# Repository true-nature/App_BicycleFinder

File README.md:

App_BicycleFinder
=================

Bicycle finder in parking area.
It works on TOCOS TWE-Lite.
You can find your bicycle by melody controlled by wireless remote commander.

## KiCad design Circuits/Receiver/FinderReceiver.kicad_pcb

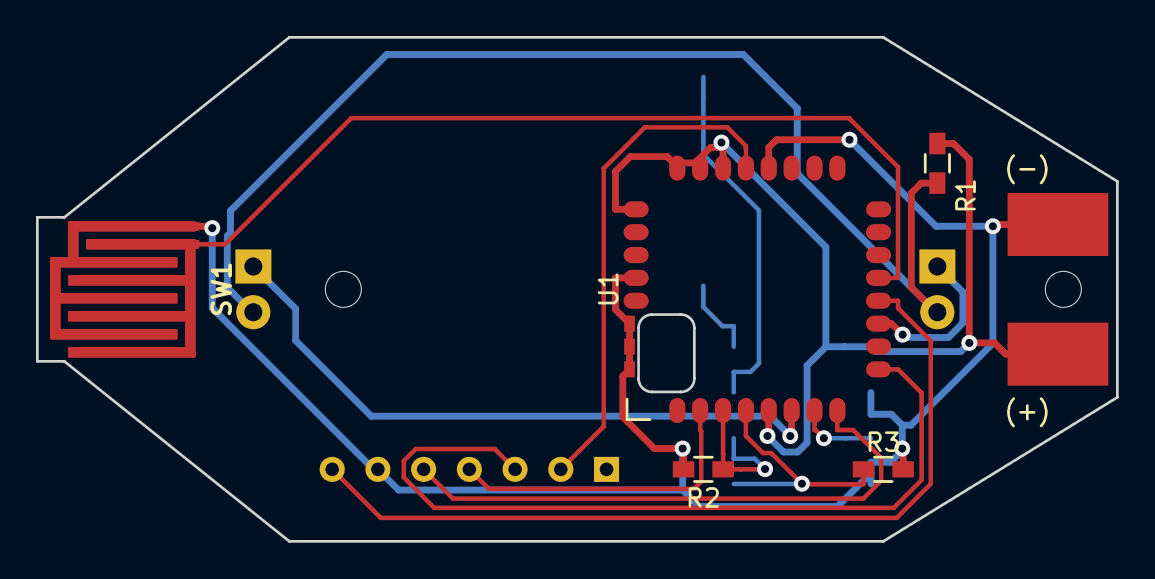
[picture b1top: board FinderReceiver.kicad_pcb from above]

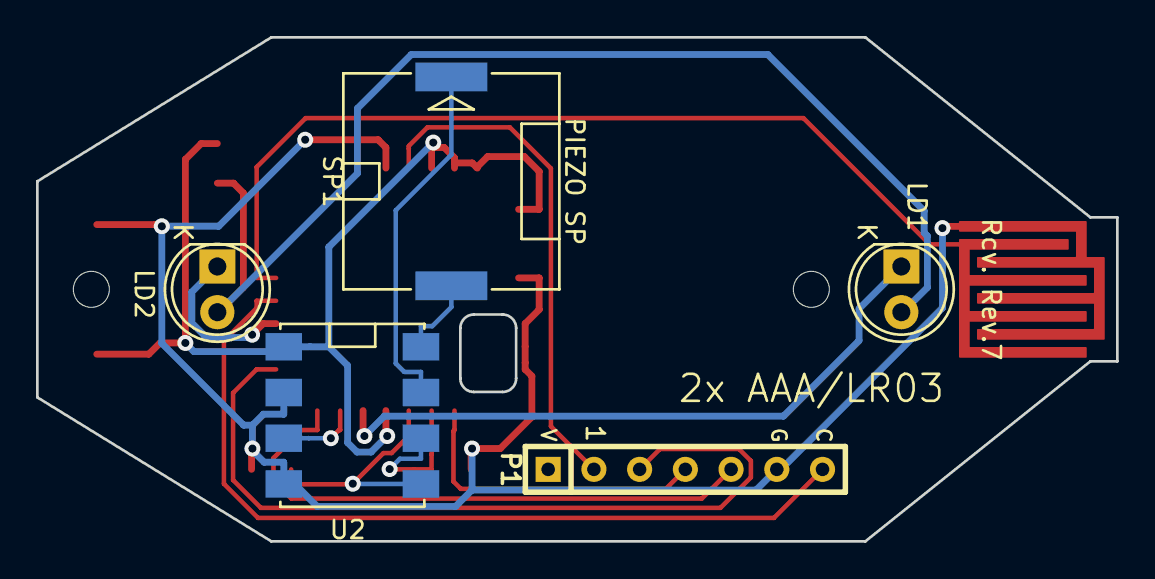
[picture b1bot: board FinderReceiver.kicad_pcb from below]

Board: 2 copper layers, 60.0 x 28.0 mm, 11 parts (6 on the bottom side), 16 nets.

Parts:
BT1: 2x AAA/LR03; FINDER_RECEIVER
LD1, LD2: LED; LED-5MM
P1: WRITER-VCC; WRITE-7P
R1: 680; R_0603_HandSoldering
R2, R3: 2M; R_0603_HandSoldering
SP1: PIEZO SP; PIEZOSPK
SW1: SW_PUSH; RUBBER_SWITCH
U1: TWE_LITE_SMD; TWE-001L-NC7
U2: NJU72501MJE; AE-NJU72501MJE

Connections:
/CFG: P1.6, U1.12
/DI1: SW1.1, U1.13
/DO3: LD1.1, U1.6
/DO4: LD2.1, U1.11
/EN1: R2.1, U1.3, U2.6
/EN2: R3.1, U1.4, U2.5
/LED: LD1.2, LD2.2, R1.2
/PRG: P1.3, U1.2
/RST: P1.1, U1.21
/RXD: P1.2, U1.9
/SOUND: U1.7, U2.3
/TXD: P1.4, U1.8
/VO1: SP1.1, U2.8
/VO2: SP1.2, U2.7
GND: BT1.2, P1.5, R2.2, R3.2, SW1.2, U1.20, U1.28, U1.30, U1.31, U1.32, U2.2, U2.4
VCC: BT1.1, R1.1, U1.5, U1.22, U1.23, U1.24, U1.25, U2.1

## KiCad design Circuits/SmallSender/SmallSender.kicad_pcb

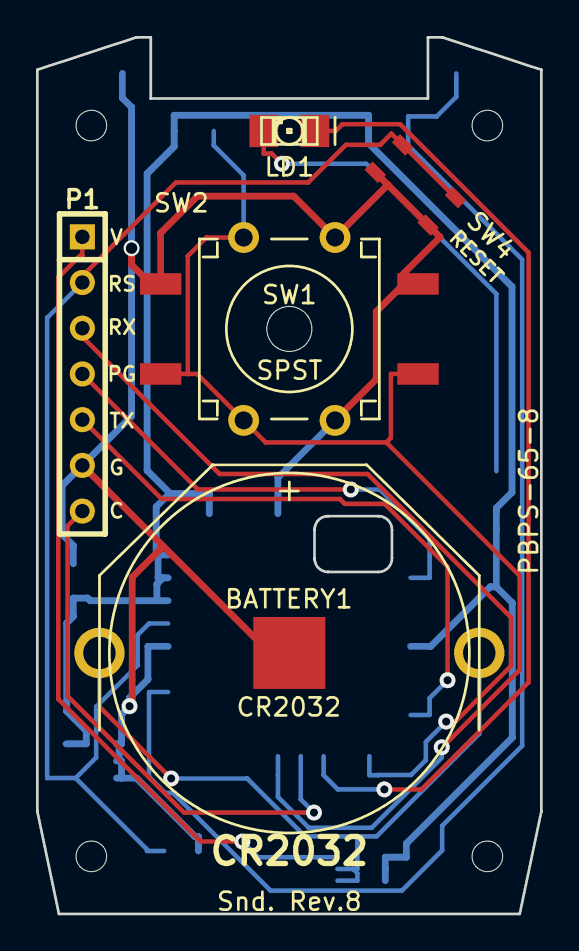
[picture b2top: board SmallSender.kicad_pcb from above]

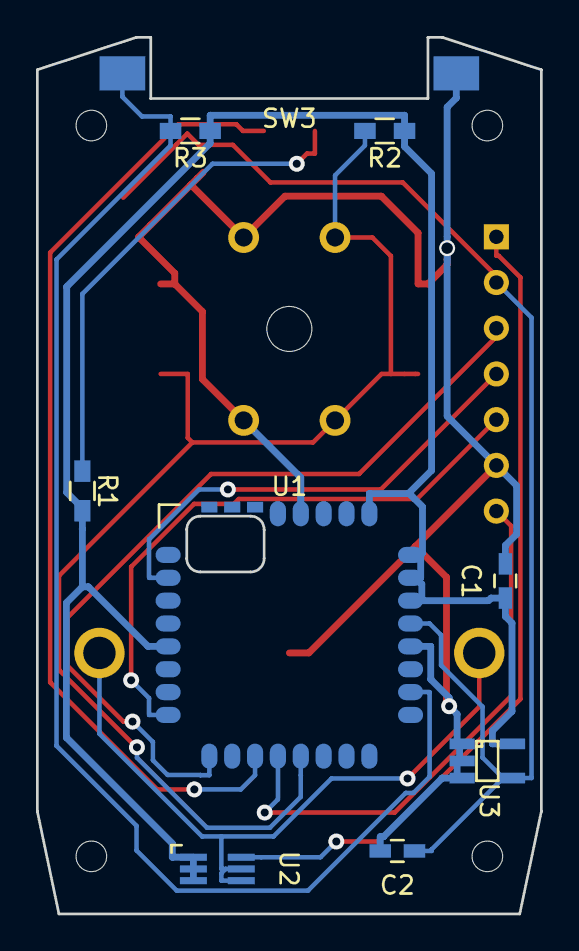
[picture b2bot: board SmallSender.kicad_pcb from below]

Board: 2 copper layers, 28.0 x 48.7 mm, 16 parts (9 on the bottom side), 13 nets.

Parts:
BATTERY1: CR2032; BK-888
C1: 10u; C_0603_HandSoldering
C2: 1000p; C_0603_HandSoldering
LD1: SML-012WT; LED-1206
P1: WRITER-VCC; WRITE-7P
PBPS-65-8: Snd. Rev.8; PBPS-65
R1: 680; R_0603_HandSoldering
R2, R3: 1M; R_0603_HandSoldering
SW1: SPST; B3FS-4002P_centerHole2_5mm
SW2: SPST; JB-15HFBP2
SW3: FR2S1015
SW4: SKRPACE010
U1: TWE_LITE_SMD; TWE-001L-NC7
U2: HN2S01FU; SC-70-6_Handsoldering
U3: BD45231G; SSOP5_Handsoldering

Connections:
/3V: BATTERY1.1, U2.4, U2.5
/CFG: P1.6, U1.12
/DI1: R2.2, SW1.1, SW2.1, U1.13
/DI4: R3.2, SW3.1, U1.18
/DO4: LD1.1, U1.11
/ExtVcc: P1.0, U2.6
/LED: LD1.2, R1.2
/PRG: P1.3, U1.2
/RST: C2.1, P1.1, SW4.1, U1.21, U3.4
/RXD: P1.2, U1.9
/TXD: P1.4, U1.8
/Vcc: C1.1, R1.1, R2.1, R3.1, U1.5, U1.22, U1.23, U1.24, U1.25, U2.1, U2.2, U2.3, U3.5
GND: BATTERY1.2, C1.2, C2.2, P1.5, SW1.2, SW2.2, SW3.2, SW4.2, U1.20, U1.28, U3.1, U3.2, U3.3

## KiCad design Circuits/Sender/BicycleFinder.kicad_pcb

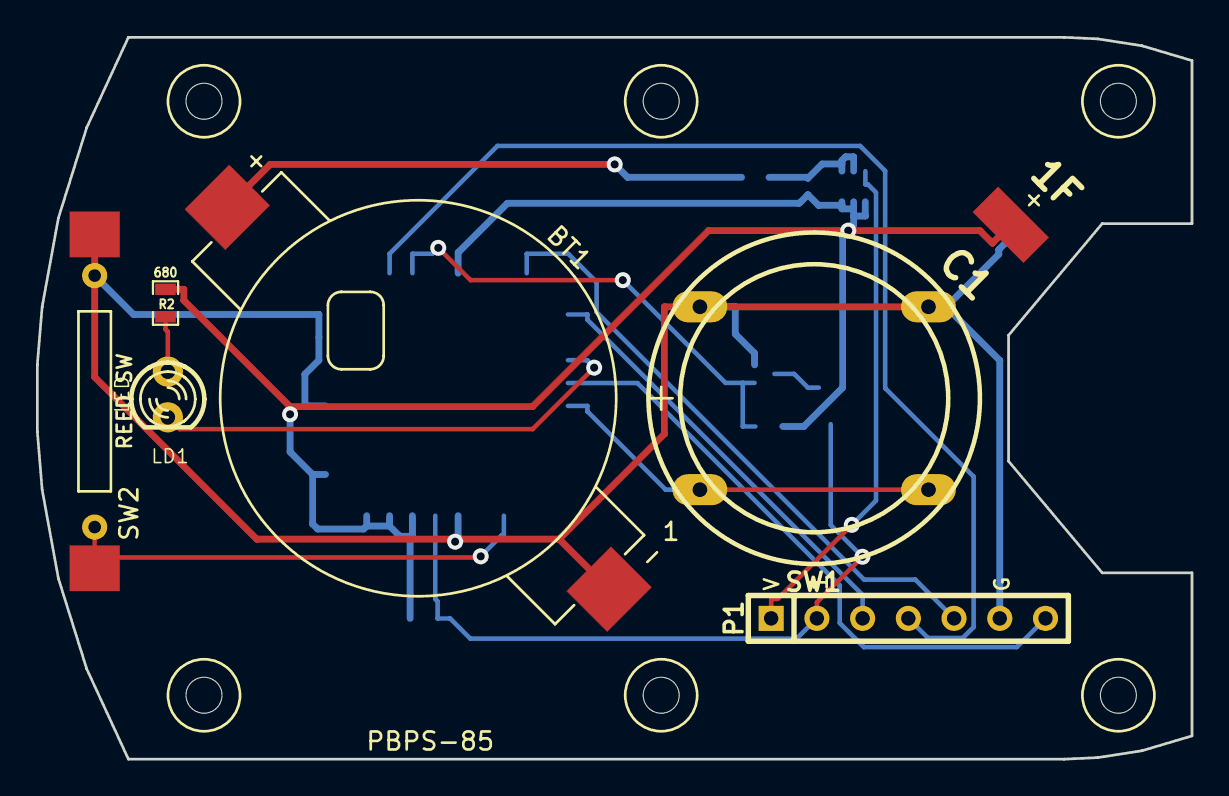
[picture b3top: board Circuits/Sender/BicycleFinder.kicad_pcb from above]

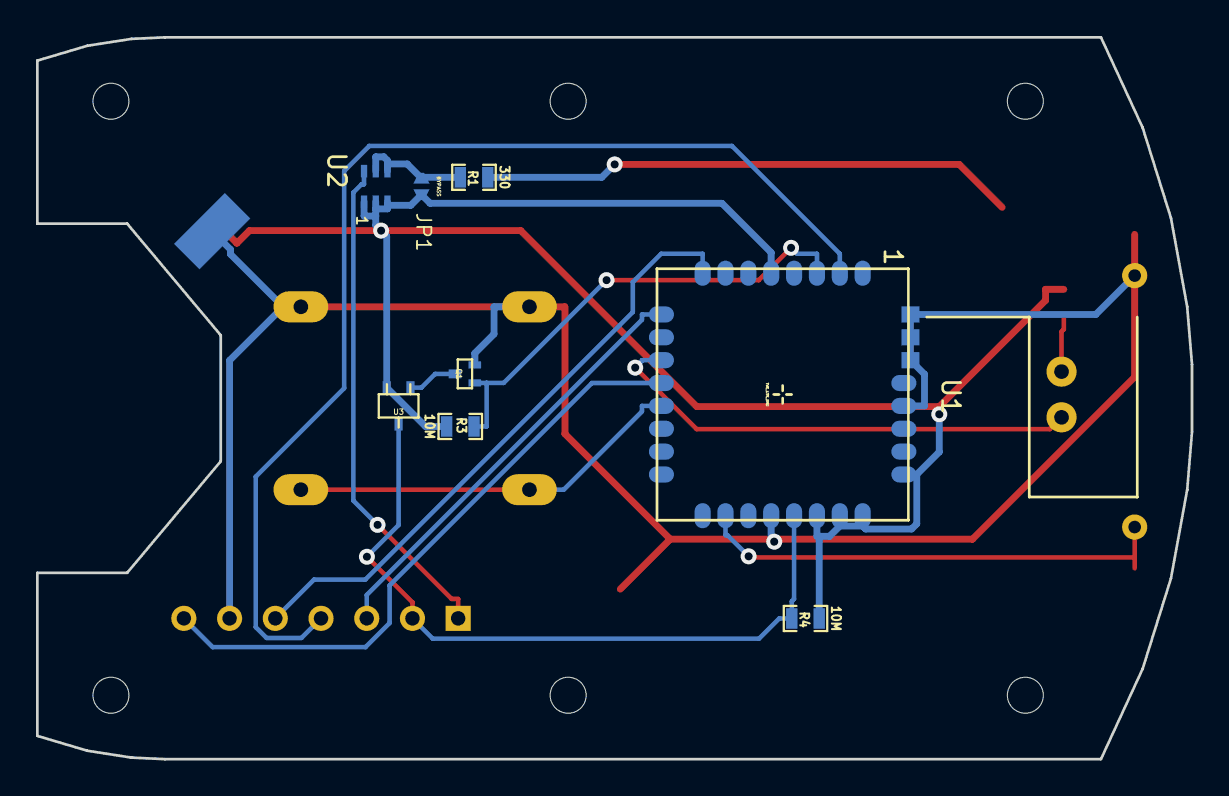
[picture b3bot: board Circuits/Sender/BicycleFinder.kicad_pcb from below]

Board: 2 copper layers, 64.1 x 40.1 mm, 16 parts (8 on the bottom side), 16 nets.

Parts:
BT1: CR2032; SMTU2032
C1: 1F; SE-5R5-D105VYV
JP1: BYPASS; JUMPER
LD1: LED; LED-3MM
P1: WRITER-VCC; WRITE-7P
PBPS-85: PBPS-85-EDLC
Q1: MOS_N; EMT3
R1: 330; SM0603_Resistor
R2: 680; SM0603_Resistor
R3, R4: 10M; SM0603_Resistor
SW1: SW_PUSH; JF-15CKCBNP2
SW2: REED SW; REEDSW
U1: TWE_LITE_SMD; TWE-001L-SMD-noNTH
U2: HN2S01FU
U3: TCM809RVNB; sc70

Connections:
/3V: BT1.1, R1.1
/CFG: P1.6, U1.12
/CHG: JP1.2, R1.2, U2.4, U2.5
/DO1: Q1.G, R3.2, U1.3
/DO4: LD1.2, U1.11
/ExVcc: P1.0, U2.6
/LED: LD1.1, R2.2
/PRG: P1.3, U1.2
/QGND: Q1.D, U3.1
/RST: P1.1, R4.2, U1.21, U3.2
/RXD: P1.2, U1.9
/STOP: SW2.1, U1.18
/TXD: P1.4, U1.8
/Vcc: C1.1, JP1.1, R2.1, R3.1, R4.1, U1.5, U1.22, U1.23, U1.24, U1.25, U2.1, U2.2, U2.3, U3.3
/WUP: SW1.1, U1.13
GND: BT1.2, C1.2, P1.5, Q1.S, SW1.2, SW2.2, U1.20, U1.28, U1.30, U1.31, U1.32

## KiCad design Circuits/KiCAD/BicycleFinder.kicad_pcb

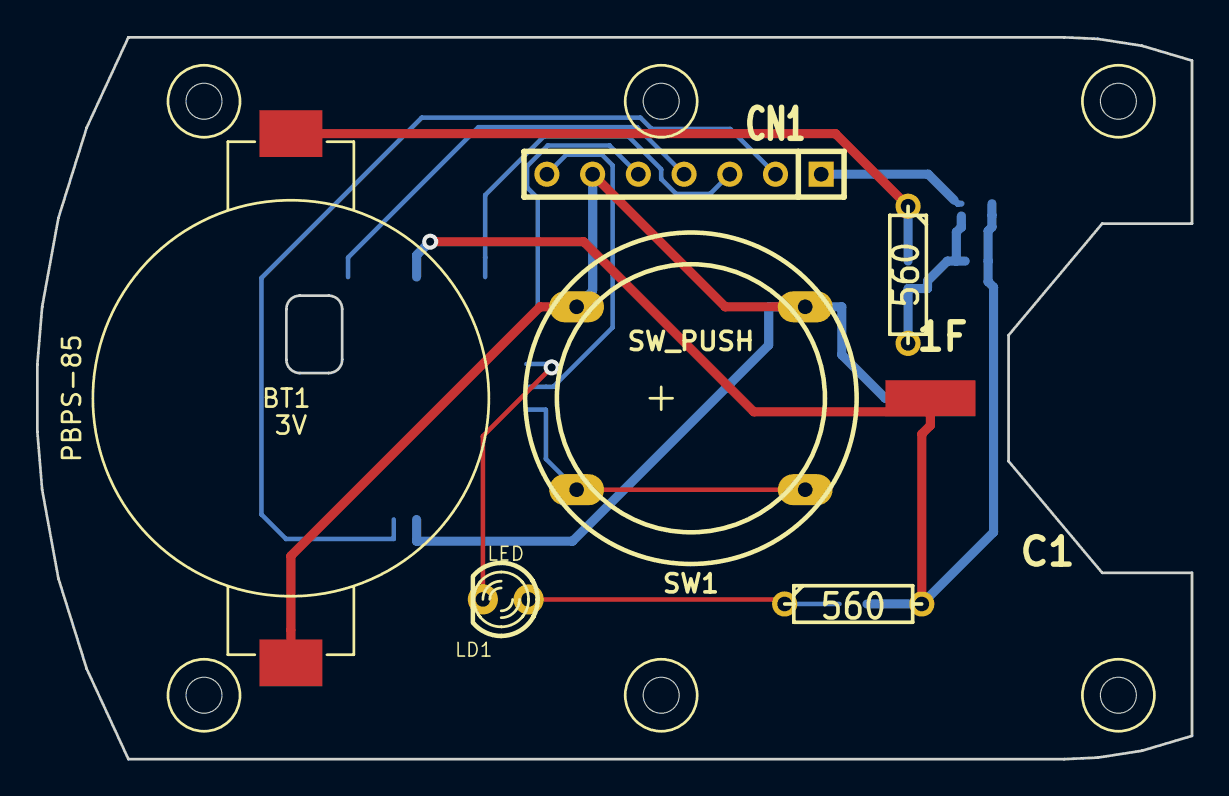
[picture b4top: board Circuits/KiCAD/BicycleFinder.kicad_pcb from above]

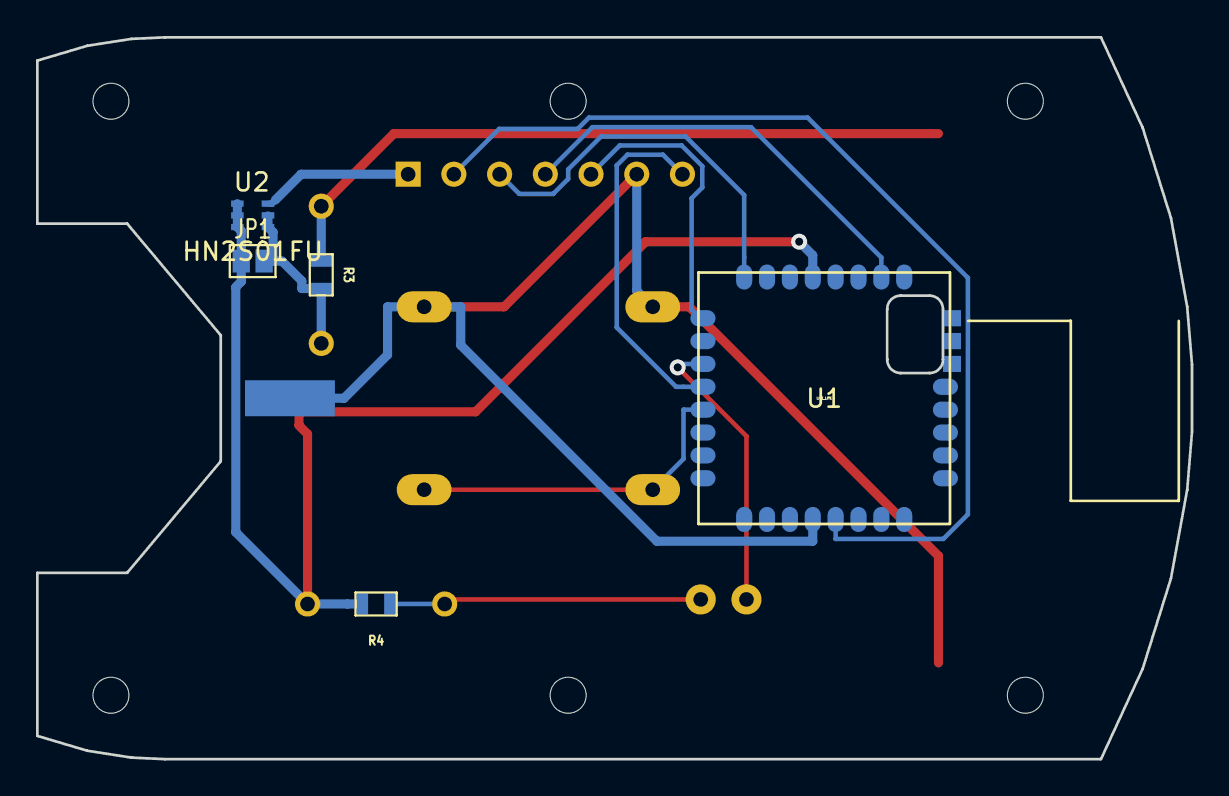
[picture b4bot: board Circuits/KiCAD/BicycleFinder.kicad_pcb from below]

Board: 2 copper layers, 64.1 x 40.1 mm, 13 parts (5 on the bottom side), 13 nets.

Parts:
BT1: 3V; SMTU2032
C1: 1F; SE-5R5-D105VYV
CN1: WRITER; SIL-7
JP1: BYPASS; GS2
LD1: LED; LED-3MM
PBPS-85: PBPS-85-EDLC
R1, R2: 560; R3
R3, R4: 560; SM0603
SW1: SW_PUSH; JF-15CKCBNP2
U1: LITE_LITE; TWE-001L-SMD
U2: HN2S01FU

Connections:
/3V: BT1.1, R1.1, R3.1
/CHG: JP1.2, R1.2, R3.2, U2.4, U2.5
/DC3V: CN1.1, U2.6
/DI1: SW1.1, U1.13
/DO4: LD1.2, U1.11
/LED: LD1.1, R2.1, R4.1
/M1: CN1.7, U1.12
/PRG: CN1.4, U1.2
/RST: CN1.2, U1.21
/RX: CN1.3, U1.8
/TX: CN1.5, U1.9
/Vcc: C1.1, JP1.1, R2.2, R4.2, U1.5, U2.1, U2.2, U2.3
GND: BT1.2, C1.2, CN1.6, SW1.2, U1.20

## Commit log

2014-09-09 App_TweLite 1.7から派生。
2014-09-09 Rename application from App_Twelite to App_BicycleFinder.
2014-09-09 Start to merge App_Melody.
2014-09-10 Merged MML implementation from App_Melody 1.3.3.
2014-09-10 スリープ抑止を開放するため、再生終了時にbHoldPlayをFALSEに変える。
2014-09-10 シリアル番号をベースにした独自のAPP_IDへ変更。
2014-09-10 1秒スリープでの受信処理を有効化。 メロディ再生中はスリープを抑止。
2014-09-10 改造部分を ENABLE_RX_ON_SLP_1SEC で切り分けた。
2014-09-10 リリースノートを独自内容に変更。
2014-09-10 Fixed typo.
2014-09-10 再生の終了待ちを独立した状態に分離。
2014-09-10 再生待ちを行うユーザー定義状態を新設。 再生の最大時間を60秒に制限。
2014-09-13 3曲目のメロディをHappy Birthdayに変更。
2014-09-13 間欠受信に失敗。
2014-09-13 他のdefineにあわせてUSE_RX_ON_SLP_1SECにrename。
2014-09-13 誤って除隊したSILENT_MODEの受信処理スキップを元に戻した。
2014-09-13 Revert "誤って除隊したSILENT_MODEの受信処理スキップを元に戻した。"
    This reverts commit 6c30a227d46dbb01fb6ffa2821d9764f91923357.
2014-09-13 SILENT_MODEと誤認して戻した変更を戻した。
2014-09-14 再生中で無い場合にLEDが一瞬点滅する場合があるバグを修正。
2014-09-14 バッテリー電圧が低下したときに点滅周期を短くする機能を追加。
2014-09-16 連続モードでもLEDを点滅させるようにした。
2014-09-17 状態遷移のタイミングをUARTに出力
2014-09-18 ADC無効化オプションが指定された場合、電源電圧だけをADC対象とする。 子機間欠モードでADC実行間隔を延長できるようにした。
2014-09-18 ADCスキップ時に受信時間を確保する。
2014-09-18 受信待ちを独立した状態で確保。
2014-09-18 連続送信を毎秒64回に増やしてWakeUp時間を減らした。
2014-09-22 再生終了時は無条件に割り込み時の再生処理を無効とする。
2014-09-22 リモコン側を子機間欠10秒モードで使用。
2014-09-23 mode4の通信間隔デフォルト値を4秒に延長。
2014-09-23 改造結果をリリースノートに反映。
2014-09-23 Bsch3vで描いた回路図を追加。
2014-09-24 SMD(QFN)版回路図を追加。
2014-09-24 QFN版DO4,GND配線ミスを修正。
2014-09-24 RESET SWを記入。
2014-09-25 未使用の宣言を削除。
2014-09-25 誤ったstatic修飾を削除。
2014-10-01 Moved circuit diagram to subdirectory.
2014-10-14 子機から子機への通信を、宛先IDによって有効とする。
2014-12-14 Restore u8Channel from EEPROM.
2014-12-15 Change operation mode to 3,4 or 7 by Device Id.
2014-12-15 Removed pull-up of analog input. Added program writer connector.
2014-12-15 Added SMD version of sender circuit.
2014-12-15 Renamed QFN to SMD.
2014-12-15 Implementing user defined MML data.
2014-12-15 Play MML in EEPROM as 1st index.
2014-12-16 コマンド0x95,0x96でMMLデータのread/writeを定義。
2014-12-16 Read/Write MML data between EEPROM and buffer.
2014-12-16 Added ToDo comments.
2014-12-16 Removed an unnecessary function.
2014-12-16 Save user MML data aligned to EEPROM segments.
2014-12-17 Fixed: Incompatible pointer.
2014-12-18 Reduced wires.
2014-12-18 Fixed: EEPROM were overwritten.
2014-12-19 Updated PNG images.
2014-12-19 Created KiCAD project file.
2014-12-19 Fit default value of the option bit for bicycle finder.
2014-12-19 Set destination id to children if sender was remote controller of bicycle finder.
2014-12-19 User more LEDs.
2014-12-20 Inverted octave up/down characters.
2014-12-20 Changed music index from FLASH[2] to EEPROM[0].
2014-12-20 Increased max length of MML string.
2014-12-20 Blink LED3, like LED4.
2014-12-20 EEPROM utility functions can read/write more than 64 bytes.
2014-12-20 子機間欠モードでチャンネル指定が有効になるようにした。
2014-12-20 Added description in header comment.
2014-12-22 Fixed: MML data was shorten before save.
2014-12-22 Disable RxEvent if mode 7(10 sec sleep mode).
2014-12-22 Split ProcessEv. vProcessEvCoreSlpSender for sender, and vProcessEvCoreSlpBeacon for receiver. Send only if bWakeupByButton is true.
2014-12-22 Continuous transmission is allowed if battery level is sufficient.
2014-12-22 Replaced voltage values to macro.
2014-12-22 Play MML only if 1sec sleep mode(mode 4).
2014-12-22 ProcessEv was opposite for mode 4 and mode 7.
2014-12-22 bWakeupByButton is not reliable. Determine to repeat or not by EDLC voltage.
2014-12-23 Saved new MML data.
2014-12-24 Updated KiCAD data.
2014-12-25 ERC passed.
2014-12-25 Added parentheses. Static analysis says that it may be a bug.
2014-12-25 Down one octave.
2014-12-25 Added arranged Canon.
2014-12-30 Made an example layout.
2015-01-04 CS75サイズ検討中。
2015-01-06 Inserted a register to reduce discharge current from CR2032.
2015-01-07 Changed pad shape to oval. Added pad 30-32.
2015-01-07 Trying layout on TAKACHI PS-85.
2015-01-07 Removed old route.
2015-01-07 Added monitor LED.
2015-01-08 Moved PS-85 shape to Edge layer.
2015-01-08 Added an antenna shape in F.Silk layer.
2015-01-08 Added 3D data of 1F EDLC designed by FreeCAD.
2015-01-09 Created a 3D shape of EDLC.
2015-01-09 Added FreeCAD 3D model of TWE-001L-SMD.
2015-01-09 Add 3D data of TWE-001L-SMD to KiCAD module.
2015-01-09 Re-converted 3D model of TWE-001L-SMD.
2015-01-10 Updated 3D model of 1F EDLC.
2015-01-10 Added 3D model of tactical switch.
2015-01-11 Colored 1F EDLC.
2015-01-12 Added 3D model of BK-888, BK-2032M, CR2032.
2015-01-12 Marked plus sign on BK-888 3D model.
2015-01-12 Swapped location of bigger parts.
2015-01-12 Moved P1 to keep distance from NTH.
2015-01-14 Fixed: Miss-connected GND line.
2015-01-14 Don't use arc in Edge.Cut layer.
2015-01-14 Renamed library (TWE-Lite -> BicycleFinder).
2015-01-14 Added a diode array.
2015-01-16 Replaced BK-888 to SMTU2032.
2015-01-16 Added 3D model of PS-85.
2015-01-18 Replaced EDLC. Moved origin of TWE-001L.
2015-01-18 Added indicator LED.
2015-01-20 Copied models from DoorChecker.
2015-01-21 Moved BSch3V data to subdirectory.
2015-01-21 Moved libraries to ../kicad-twe.
2015-01-29 Reviewed parts layout.
2015-01-30 Changed current restriction register value.
2015-01-30 Moved some chip parts.
2015-01-31 Moved pin names of writer to F.Silk layer.
2015-02-06 Moved location of 3D models.
2015-02-06 Saved 3D preview images.
2015-02-08 発信前にチャタリング防止。空振り対策のため1/64秒毎に発信。
2015-02-15 Started to design the receiver.
2015-02-17 Locate the TWE-Lite SMD on the front side.
2015-02-17 Added spare footprints.
2015-02-18 Fixed: LED location.
2015-02-18 Added sender with a reed switch.
2015-02-18 Started to design a PCB.
2015-02-20 Replaced EDLC.
2015-02-20 Added a 3D model of PS-65.
2015-02-21 Changed battery holder. Added more EDLC.
2015-02-22 Changed EDLC.
2015-02-22 Pullup all analog inputs.
2015-02-23 Reload net list.
2015-02-24 Modified some connections.
2015-02-24 Fixed: Sound output is connected to PWM1.
2015-02-24 Fixed: Model with NPH hole.
2015-02-26 Reviewing connections.
2015-02-28 Sleep immediately after brownout reset.
2015-03-01 Updated connections.
2015-03-01 Disabled brown out detection.
2015-03-01 Added reset monitor.
2015-03-02 Added voltage monitor.
2015-03-02 Replaced TWE-Lite module.
2015-03-03 Disable reset monitor after boot.
2015-03-03 Stop MML if DI4 was asserted. Added MML bank.
2015-03-04 Relocated the reset monitor.
2015-03-04 Send MML in transmission state triggered by HwEvent.
2015-03-04 Update when both DI1 and DI4 were pushed.
2015-03-05 Save MML index to EEPROM.
2015-03-05 Renamed the elements of MML array.
2015-03-05 Added more MML data.
2015-03-05 Removed an unused connection.
2015-03-09 Omit external pull-up registers.
2015-03-09 Copied slave from master.
2015-03-10 Modified configurations to build Slave binary.
2015-03-10 Removed unused lines.
2015-03-10 Replaced tactical switch to SMD type.
2015-03-11 Renamed source code that contains melody archive.
2015-03-11 Removed unused functions.
2015-03-11 Use fixed dst id.
2015-03-16 Start to edit by KiCad nightly build.
2015-03-16 Replaced to current footprint modules.
2015-03-21 Switch GND by a voltage detector.
2015-03-21 Skip to restore DO1 status.
2015-03-22 Moved LED to front side.
2015-03-22 Blink secondary LED connected to DO3.
2015-03-22 Leave DO1 state high.
2015-03-22 Increased duration of transmission.
2015-03-22 Removed piezo speaker on front side.
2015-03-22 Increased waiting time for play command.
2015-03-22 Added library table.
2015-03-22 Removed old big sender.
2015-03-28 Changed library file name from TWE-Lite to favorites.
2015-03-29 Changed library file name from TWE-Lite to favorites. Added NJU72501MJE piezo speaker driver.
2015-03-29 Control EN2 by DO2 GPIO instead of a jumper.
2015-03-29 Relocated module path.
2015-03-30 Fast blink only if battery voltage itself is low.
2015-04-12 Updated 3d models.o
2015-04-19 Added NJU72501 charge pump module.
2015-04-19 Run PWM timer while playing MML only.
2015-04-20 Added reset switch to sender.
2015-04-21 Added SMD tactical switch.
2015-04-21 Fixed: Obsoleted battery symbol.
2015-04-25 Added RESET rubber switch.
2015-04-26 Replaced footprint of SMD register.
2015-05-06 Fixed 3D footprint path.
2015-06-08 Changed LED symbol and register value.
2015-06-08 Removed reset switch and connected SW1 to DI1.
2015-06-09 Relocated all parts.
2015-06-09 Relocated base PCB.
2015-06-09 Artwork in progress.
2015-06-10 Shrunk rubber switch pattern.
2015-06-10 Changed location of parts.
2015-06-14 Replaced outline edge.
2015-06-14 Fixed operation mode. Switch config mode by PORT_CONF1.
2015-06-14 Fixed operation mode of master side. Switch config mode by PORT_CONF1.
2015-06-14 Implementing LED flasher mode.
2015-06-14 Reduce CPU clock when flasher mode.
2015-06-15 ToDoコメントを追加。
2015-06-17 Connect DO1 to EN1.
2015-06-18 Added pull down registers.
2015-06-20 Changed size of pad holes.
2015-06-25 Send event in cbToCoNet_vHwEvent(). Read sleep length from table.
2015-06-28 Worked LED flasher mode.
2015-06-28 Changed flasher led pattern.
2015-06-28 Changed value of option flags.
2015-06-28 Fixed variable declarations.
2015-06-29 Enable EN1 and EN2 on test play.
2015-06-30 Replaced the reset IC.
2015-07-01 Replaced reset IC.
2015-07-01 Added pull-down register and buffer capacitor.
2015-07-01 Manage timeout by counter.
2015-07-02 Determine default AppId and channel from serial number.
2015-07-02 Relocated some parts.
2015-07-03 Hide footprint names.
2015-07-03 Changed register value.
2015-07-04 Updated footprints.
2015-07-07 Added dual SPST dip switch.
2015-07-10 Send 32 times per second with 1 retry.
2015-07-12 Fixed: Kathode mark was opposite.
2015-07-12 Initialize PWM sate low.
2015-07-18 Mute NJU72501MJE on boot.
2015-07-19 Swap TWE-Lite and PIEZO Speaker.
2015-07-25 Fixed: A slave responses IO packet from other slaves.
2015-07-25 Changed text in silk.
2015-08-09 Changed battery threshold.
2015-08-16 Continue if battery level is low.
2015-08-16 Use CR2032 instead of CR1220.
2015-10-12 Use calculated CRC.
2015-10-12 Clear sSerSeqRx only if all fragmented data was received.
2015-10-12 Save current layout.
2015-10-15 Disable low latency input by default.
2015-12-06 Connect SW3 to M2.
2015-12-07 Changed location of a tactical switch.
2015-12-13 Added drill center hole.
2015-12-14 Added state chart diagram.
2016-01-06 Duplicated trigger tactical switch.
2016-01-11 Rerouted.
2016-02-03 Removed state chart diagram.
2016-02-03 Start to implement experimental auto pairing.
2016-02-04 Set AppId,Ch and TxPower for pairing.
2016-02-07 Added vReceivePairingData().
2016-02-08 Resolved warnings.
2016-02-08 Defined members for auto pairing.
2016-02-09 Implementation of auto pairing is in progress.
2016-02-11 Copy auto pairing functions to Master side.
2016-02-11 Blink LED while auto pairing.
2016-02-14 Debugging auto pairing.
2016-02-15 AppContext.u32AppId should not change after ToCoNet_vMacStart.
2016-02-15 Auto pairing worked.
2016-02-15 Check timeout at E_EVENT_TICK_TIMER.
2016-02-16 Stop to receive before SetState.
2016-02-18 Change RF settings before state transition.
2016-02-18 Added voltage detector.
2016-02-26 Added a voltage detector.
2016-02-26 Added 3D shape of a SMD LED.
2016-02-26 Moved location of LED reference.
2016-02-28 Added external pull-up register.
2016-02-29 Renamed the folder name of 3d shapes.
2016-03-03 Down the battery alert level.
2016-03-06 Disabled deep sleep. Changed key assign of auto pairing.
2016-03-06 Connect SW4 to RESET instead of M2.
2016-04-07 Changed directory name of 3D shapes.
2016-04-13 Added silent melody. Removed volume switch(SW2) from receiver.
2016-05-08 Removed the net list files.
2016-06-21 経過時間の判定をE_EVENT_TICK_TIMERで行う。
2016-06-26 Defined ADC state constants.
2016-06-26 Increased the length of chattering check wait.
2016-06-26 Increased chattering check counter.
2016-10-21 Toss a random number in pairing process.
2017-01-22 不感時間を設けてチャタリングの影響を回避。
2017-01-22 KiCadとEclipsewをアップデート。
